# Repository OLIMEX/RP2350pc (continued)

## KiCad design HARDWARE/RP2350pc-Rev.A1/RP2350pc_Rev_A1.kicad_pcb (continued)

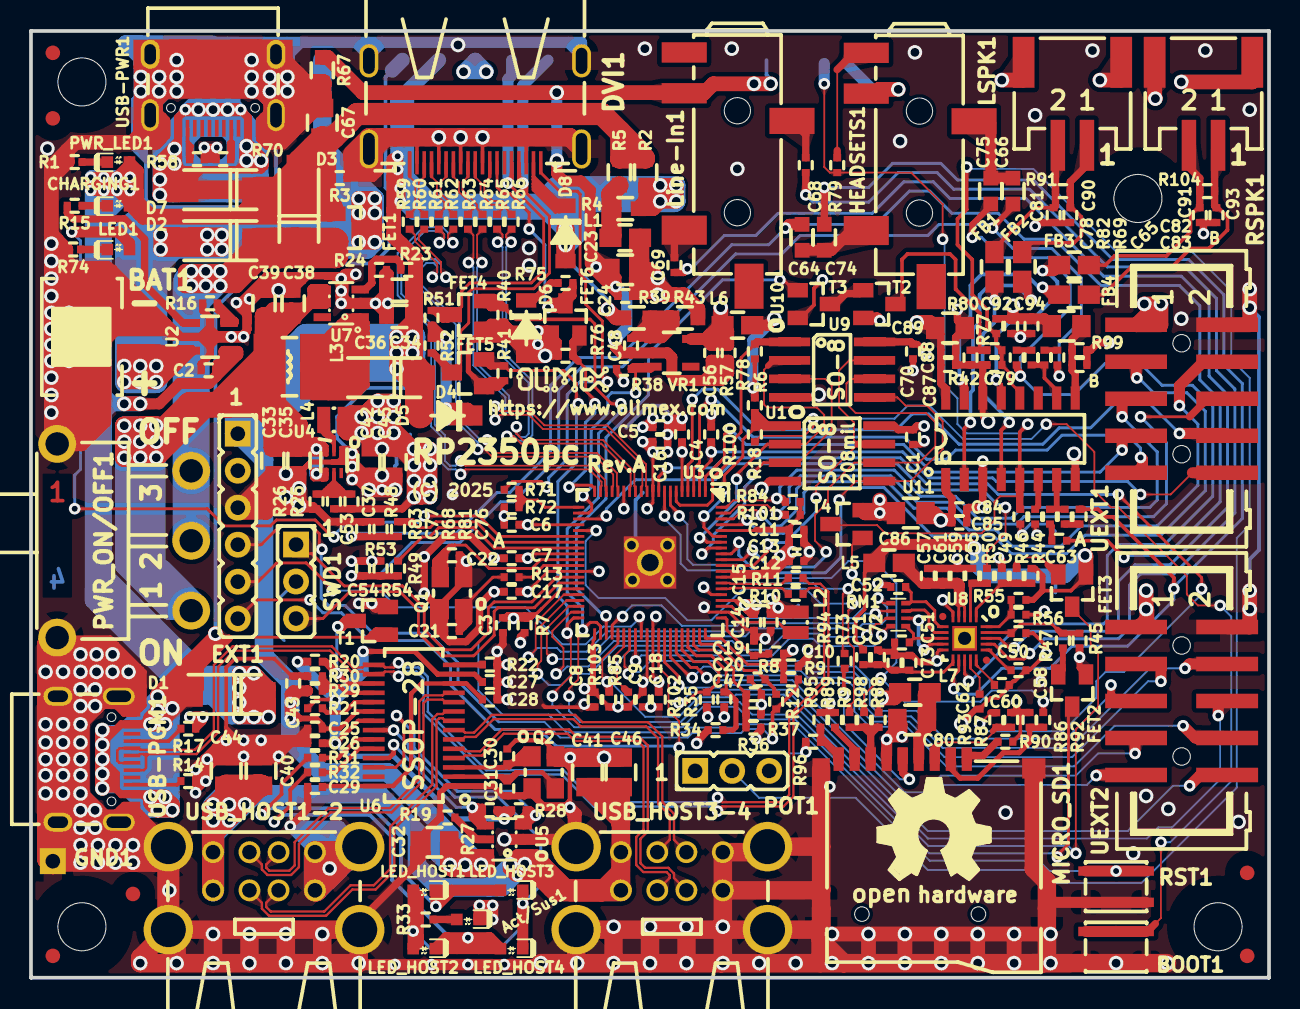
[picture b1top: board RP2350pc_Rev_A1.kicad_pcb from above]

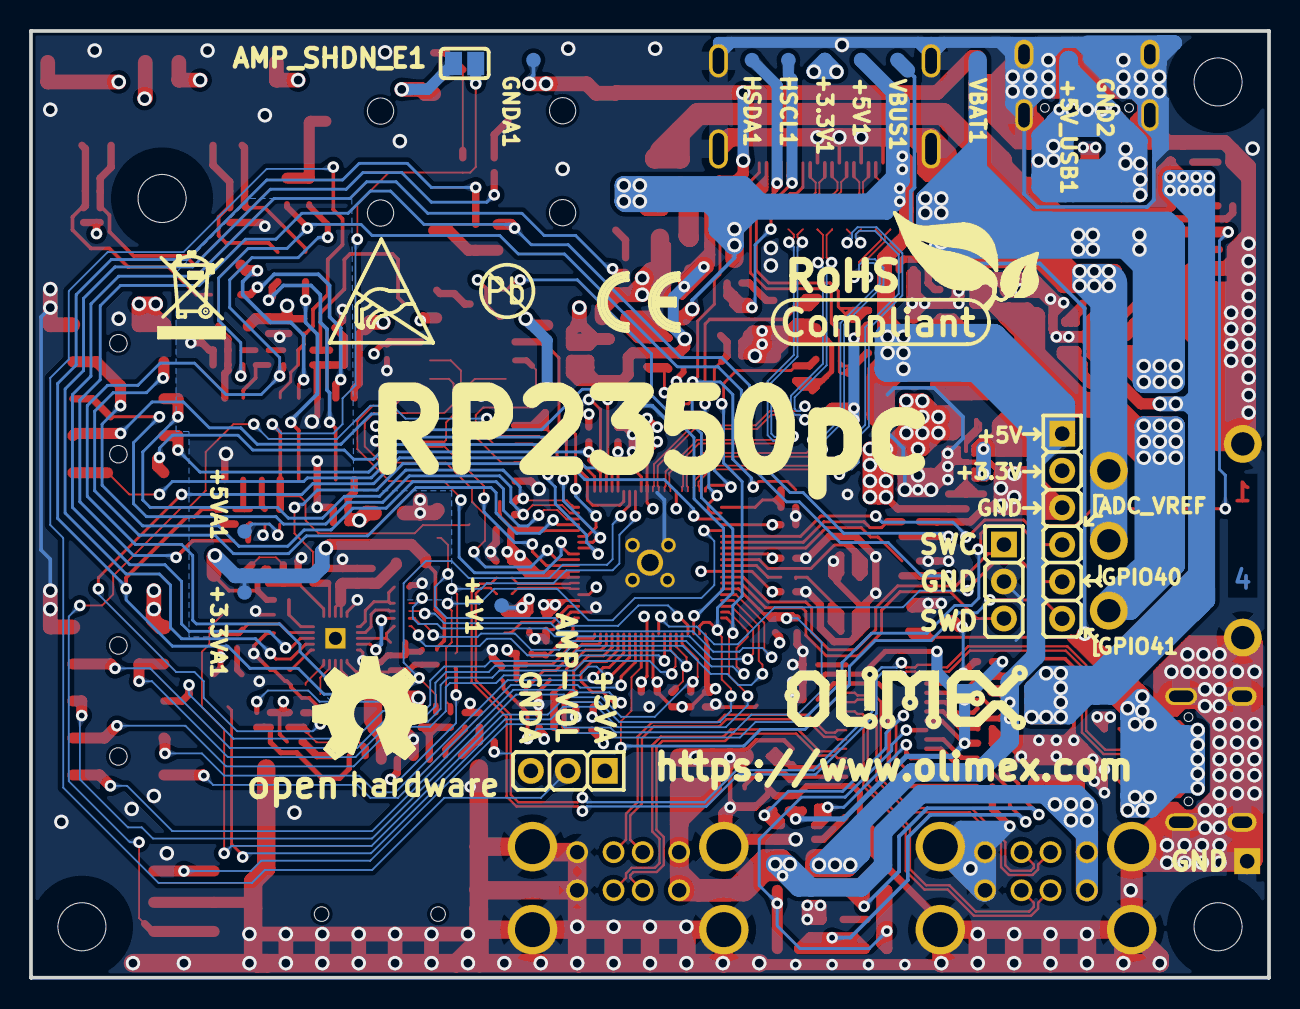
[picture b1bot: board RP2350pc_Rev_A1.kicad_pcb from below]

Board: 4 copper layers, 85.0 x 65.0 mm, 302 parts (20 on the bottom side), 191 nets.

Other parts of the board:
Logo_OLIMEX_80: Logo_OLIMEX_80
Logo_OLIMEX_TB: Logo_OLIMEX_TB
Sign_Antistatic: Sign_Antistatic
Sign_CE: CE_Sign
Sign_OSHW_8x8, Sign_OSHW_8x8-Top: Sign_OSHW_8x8
Sign_PB-Free: Sign_PB-Free
Sign_RecycleBin: Sign_RecycleBin; Sign_RecycleBin_1
Sign_RoHS: Sign_RoHS; Sign_RoHS_1

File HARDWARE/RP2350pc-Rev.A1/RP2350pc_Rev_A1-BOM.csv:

"Id";"Designator";"Footprint";"Quantity";"Designation";"Supplier and ref";
1;"MH1,MH3,MH4,MH2";"Mounting_Hole_Drill-3.3mm_Clerance-7mm";4;"Drill(3.3mm)/Restrict(7.00mm)";;;
2;"R84,R101,R15,R103,R52,R76,R33,R40,R85,R32,R71,R51,R44,R31,R74,R1,R41,R45,R34";"R_0402_5MIL_DWS";19;"2.2k/R0402";;;
3;"R53,R54";"R_0402_5MIL_DWS";2;"150R/R0402";;;
4;"R48,R66,R63,R60,R59,R62,R61,R64,R65,R49";"R_0402_5MIL_DWS";10;"270R/R0402";;;
5;"FID5,FID6,FID4";"Fiducial1x3";3;"Fiducial";;;
6;"FID2,FID3,FID1";"Fiducial1x3_Paste";3;"Fiducial";;;
7;"C53,C8,C4,C13,C61,C27,C70,C5,C29,C24,C10,C7,C11,C12,C6,C83,C9,C18,C54,C47,C43,C16,C1,C73,C59";"C_0402_5MIL_DWS";25;"100nF/10V/20%/X5R/C0402";;;
8;"BOOT1,RST1";"YTS-A016-X";2;"YTS-A016-X";;;
9;"SWD1,POT1";"HN1x3";2;"NA(HN1x3)";;;
10;"DVI1";"HDMI-SWM-19_Paste";1;"HDMI-SWM-19";;;
11;"R11,R10";"R_0402_5MIL_DWS";2;"27R/R0402";;;
12;"C45,C39,C34,C33";"C_0603_5MIL_DWS";4;"NA(22uF/6.3V/20%/X5R/C0603)";;;
13;"C65,C78,C60,C77,C68,C2,C58,C87,C63,C62,C76,C82,C79,C72,C69,C84";"C_0402_5MIL_DWS";16;"1uF/6.3V/10%/X5R/C0402";;;
14;"R80,R25";"R_0402_5MIL_DWS";2;"220k/R0402";;;
15;"R24";"R_0402_5MIL_DWS";1;"1.05k/1%/R0402";;;
16;"R38,R35,R72,R29,R90,R87,R86,R89,R88";"R_0402_5MIL_DWS";9;"4.7k/R0402";;;
17;"USB_HOST1-2,USB_HOST3-4";"USB_TWO_LEVEL";2;"USBB1-FRWH-4A(USB-Ax2)";;;
18;"LED_HOST4,LED_HOST3,LED1,LED_HOST1,LED_HOST2";"LED_0603_KA";5;"LED/GREEN/0603";;;
19;"U1";"SO-8_208mil";1;"W25Q128JVSIQ(SOIC-8_208mils)";;;
20;"FB1,FB3,FB2,L7,L1,FB4,L5";"L_0805_5MIL_DWS";7;"FB0805/600R/2A";;;
21;"R99";"R_0805_5MIL_DWS";1;"100R/R0805";;;
22;"C89,C40,C86,C67,C41";"C_0805_5MIL_DWS";5;"NA(47uF/6.3V/20%/X5R/C0805)";;;
23;"C52,C22,C51,C21,C55";"C_0402_5MIL_DWS";5;"27pF/50V/5%/C0G/C0402";;;
24;"C15,C14,C20,C19,C17";"C_0402_5MIL_DWS";5;"4.7uF/10V/20%/X5R/C0402";;;
25;"U4";"SOT-563-6";1;"TPS62A02ADRLR(SOT-563-6)";;;
26;"Line-In1,HEADSETS1";"PJ-W47S-05D2-LF_5PIN_V2_LongerPads";2;"PJ-W47S-05D2-LF";;;
27;"R2,R5,R39";"R_0603_5MIL_DWS";3;"NA(0R/R0603)";;;
28;"C85,C71,C88,C48,C56,C26,C28,C25";"C_0402_5MIL_DWS";8;"10uF/6.3V/20%/X5R/C0402";;;
29;"R46,R97,R79,R92,R47,R93,R50,R94,R8";"R_0402_5MIL_DWS";9;"33R/R0402";;;
30;"R95";"R_0402_5MIL_DWS";1;"NA(4.7k/R0402)";;;
31;"FET2,FET5,FET4,FET6,FET3";"SOT23";5;"BSS138(SOT23-3)";;;
32;"C44,C32,C80,C46,C23";"C_0805_5MIL_DWS";5;"47uF/6.3V/20%/X5R/C0805";;;
33;"MICRO_SD1";"TFC-WPAPR-08";1;"TFC-WPAPR-08-LF";;;
34;"C35,C38,C75,C66,C64,C74,C42,C36";"C_0603_5MIL_DWS";8;"22uF/6.3V/20%/X5R/C0603";;;
35;"R70,R58,R17,R14";"R_0402_5MIL_DWS";4;"5.1k/1%/R0402";;;
36;"U2";"SOT-23-5";1;"TP4054-42-SOT25-R(SOT23-5)";;;
37;"LSPK1,RSPK1";"PH2.0-2PWB";2;"PH2.0-2PWB";;;
38;"R27,R20,R56,R68,R81,R6,R30,R28,R57,R16,R21,R78,R77,R82,R69,R3";"R_0402_5MIL_DWS";16;"10k/R0402";;;
39;"L6";"L_0805_5MIL_DWS";1;"NA(FB0805/600R/2A)";;;
40;"CHARGING1";"LED_0603_KA";1;"LED/YELLOW/0603";;;
41;"D7";"SMA-KA";1;"NA(1N5822/SS34/SMA)";;;
42;"UEXT1,UEXT2";"GBH-254-SMT-10";2;"P-B-V-10-LF";;;
43;"C93,C90,C81,C91";"C_0402_5MIL_DWS";4;"270pF/50V/5%/C0G/C0402";;;
44;"U10";"SO-8";1;"APS6404L-3SQR-SN(SOIC-8_150mils)";;;
45;"U9";"SO-8_208mil";1;"NA(W25Q128JVSIQ(SOIC-8_208mils))";;;
46;"R37,R36";"R_0402_5MIL_DWS";2;"470k/R0402";;;
47;"GND1";"TEST_PAD40x70_SQUARE";1;"TESTPAD";;;
48;"R55";"R_0402_5MIL_DWS";1;"NA/R0402";;;
49;"EXT1";"HN1x6";1;"NA(HN1x6)";;;
50;"C94,C3";"C_0402_5MIL_DWS";2;"NA(100nF/10V/20%/X5R/C0402)";;;
51;"T2";"SOT23";1;"LMUN2111LT1G(SOT-23)";;;
52;"C92";"C_0402_5MIL_DWS";1;"NA(1uF/6.3V/10%/X5R/C0402)";;;
53;"R83,R75";"R_0402_5MIL_DWS";2;"27k/R0402";;;
54;"U6";"SSOP28_10x4mm_Pitch_0.64mm";1;"FE1.1s(SSOP-28)";;;
55;"D4,D3,D1,D2";"SMA-KA";4;"1N5822/SS34/SMA";;;
56;"Act/Sus1,PWR_LED1";"LED_0603_KA";2;"LED/RED/0603";;;
57;"T1,T3,T4";"SOT23";3;"LMUN2235LT1G(SOT-23)";;;
58;"U7";"SOT23-6";1;"MT3608(SOT23-6)";;;
59;"R13,R18,R104,R91,R42";"R_0402_5MIL_DWS";5;"1k/R0402";;;
60;"U5";"SOT23-6";1;"CH217K(SOT23-6L)";;;
61;"R9";"R_0402_5MIL_DWS";1;"200R/1%/R0402";;;
62;"R43,R4,R67";"R_0603_5MIL_DWS";3;"0R/R0603";;;
63;"R102,R100,R7";"R_0402_5MIL_DWS";3;"NA(10k/R0402)";;;
64;"Q2,Q1";"TSX-3.2x2.5mm_GND(3)";2;"Q12MHz/18pF/30ppm/4P/3.2x2.5mm(ABM8-12.000MHZ-D2Y-T)";;;
65;"R12";"R_0402_5MIL_DWS";1;"1.3R/1%/R0402";;;
66;"USB-PGM1,USB-PWR1";"USB2.0_TYPE-C(A40-00119-A52-12)_Paste";2;"USB-C-16P-F(A40-00119-A52-12)";;;
67;"FET1";"SOT23";1;"IRLML6402TRPbF";;;
68;"RM1";"RA0805_(4X0402)_xx_BIGGEROUTPADS";1;"RA0805_(4X0402)_33R";;;
69;"C49,C50";"C_0402_5MIL_DWS";2;"20pF/50V/5%/NP0/C0402";;;
70;"D5,D6,D8";"SOD-123_1C-2A_KA";3;"1N5819S4/SOD123";;;
71;"R22";"R_0402_5MIL_DWS";1;"2.7k/1%/R0402";;;
72;"R73";"R_0402_5MIL_DWS";1;"10R/R0402";;;
73;"C30,C31";"C_0402_5MIL_DWS";2;"NA(27pF/50V/5%/C0G/C0402)";;;
74;"L2";"L_2016_MM";1;"3.3uH/2.0A/DCR=140mR/20%/2.00x1.60x1.00mm/L2016(PIM201610-3R3MTS00)";;;
75;"R26,R19";"R_0402_5MIL_DWS";2;"49.9k/1%/R0402";;;
76;"PWR_ON/OFF1";"SS-12D11G5";1;"SS-12D11G5";;;
77;"R96,R98";"R_0402_5MIL_DWS";2;"NA(33R/R0402)";;;
78;"U11";"SO-16";1;"PAM8003DR(SO-16)";;;
79;"C37";"C_0402_5MIL_DWS";1;"NA(120pF/50V/5%/C0G/C0402)";;;
80;"U8";"QFN-20_EP(21)_3x3x0.6mm_Pitch_0.4mm";1;"ES8311(QFN-20)";;;
81;"R23";"R_0402_5MIL_DWS";1;"8.25k/1%/R0402";;;
82;"L4";"L_2016_MM";1;"1.0uH/4.2A/DCR=35mR/20%/2.00x1.60x1.00mm/L2016(PIM201610-1R0MTS00)";;;
83;"L3";"CD42(43)";1;"4.7uH/2.33A/DCR=70mR/20%/CD43(NRS4018T4R7MDGJ)";;;
84;"BAT1";"PH2.0-2AT(BAT)";1;"PH2.0-2AT";;;
85;"U3";"QFN-80_10.00x10.00x0.90mm_P0.4mm";1;"RP2350B-A4(QFN-80_10.00x10.00x0.90mm_P0.4mm)";;;
86;"C57";"C_0402_5MIL_DWS";1;"NA(10uF/6.3V/20%/X5R/C0402)";;;
87;"VR1";"SOT-23-5";1;"AP1231-3.3V(SOT23-5)";;;
88;"HSDA1,HSCL1,+5V_USB1,GNDA1,GND2,VBUS1,+5V1,+5VA1,+1V1,+3.3VA1,VBAT1,+3.3V1";"TESTPAD_40-ROUND";12;"TESTPAD";;;
89;"AMP_SHDN_E1";"SJ";1;"Opened";;;

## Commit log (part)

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2025-06-16 initial upload
2025-07-01 add user manual
